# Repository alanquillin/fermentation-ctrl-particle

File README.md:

# fermentation-controller

A Particle project named fermentation-controller

## Welcome to your project!

Every new Particle project is composed of 3 important elements that you'll see have been created in your project directory for fermentation-controller.

#### ```/src``` folder:  
This is the source folder that contains the firmware files for your project. It should *not* be renamed. 
Anything that is in this folder when you compile your project will be sent to our compile service and compiled into a firmware binary for the Particle device that you have targeted.

If your application contains multiple files, they should all be included in the `src` folder. If your firmware depends on Particle libraries, those dependencies are specified in the `project.properties` file referenced below.

#### ```.ino``` file:
This file is the firmware that will run as the primary application on your Particle device. It contains a `setup()` and `loop()` function, and can be written in Wiring or C/C++. For more information about using the Particle firmware API to create firmware for your Particle device, refer to the [Firmware Reference](https://docs.particle.io/reference/firmware/) section of the Particle documentation.

#### ```project.properties``` file:  
This is the file that specifies the name and version number of the libraries that your project depends on. Dependencies are added automatically to your `project.properties` file when you add a library to a project using the `particle library add` command in the CLI or add a library in the Desktop IDE.

## Adding additional files to your project

#### Projects with multiple sources
If you would like add additional files to your application, they should be added to the `/src` folder. All files in the `/src` folder will be sent to the Particle Cloud to produce a compiled binary.

#### Projects with external libraries
If your project includes a library that has not been registered in the Particle libraries system, you should create a new folder named `/lib/<libraryname>/src` under `/<project dir>` and add the `.h`, `.cpp` & `library.properties` files for your library there. Read the [Firmware Libraries guide](https://docs.particle.io/guide/tools-and-features/libraries/) for more details on how to develop libraries. Note that all contents of the `/lib` folder and subfolders will also be sent to the Cloud for compilation.

## Compiling your project

When you're ready to compile your project, make sure you have the correct Particle device target selected and run `particle compile <platform>` in the CLI or click the Compile button in the Desktop IDE. The following files in your project folder will be sent to the compile service:

- Everything in the `/src` folder, including your `.ino` application file
- The `project.properties` file for your project
- Any libraries stored under `lib/<libraryname>/src`

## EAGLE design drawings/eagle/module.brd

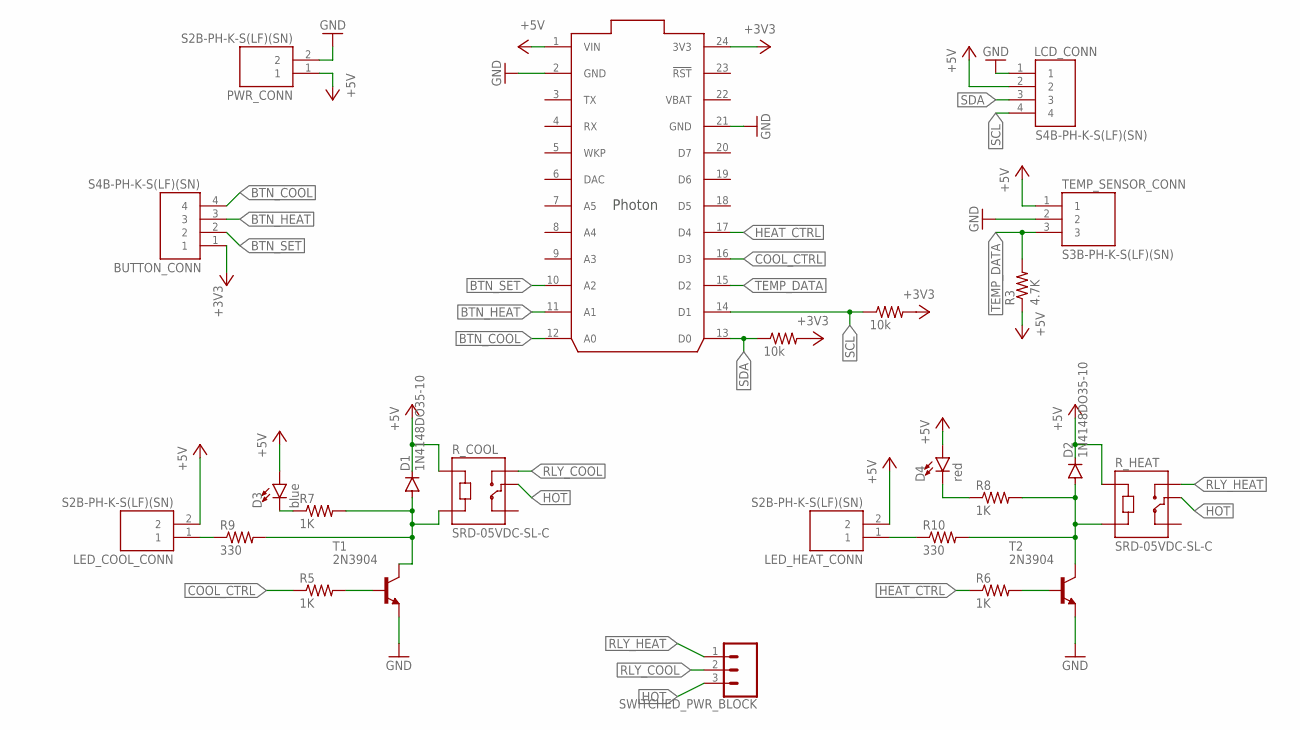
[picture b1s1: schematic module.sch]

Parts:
BUTTON_CONN: S4B-PH-K-S(LF)(SN); JST_S4B-PH-K-S(LF)(SN); MPN S4B-PH-K-S (LF)(SN)
D1, D2: 1N4148DO35-10; DO35-10; MPN 1N4148 (DO-35)
D3: blue; LED_3MM; MPN TLHB4400
D4: red; LED_3MM; MPN 4300F1LC
LCD_CONN: S4B-PH-K-S(LF)(SN); JST_S4B-PH-K-S(LF)(SN); MPN S4B-PH-K-S (LF)(SN)
LED_COOL_CONN: S2B-PH-K-S(LF)(SN); JST_S2B-PH-K-S(LF)(SN); MPN S2B-PH-K-S (LF)(SN)
LED_HEAT_CONN: S2B-PH-K-S(LF)(SN); JST_S2B-PH-K-S(LF)(SN); MPN S2B-PH-K-S (LF)(SN)
PWR_CONN: S2B-PH-K-S(LF)(SN); JST_S2B-PH-K-S(LF)(SN); MPN S2B-PH-K-S (LF)(SN)
R1, R2: 10k; 0207/10
R3: 4.7K; 0207/10
R5, R6, R7, R8: 1K; 0207/10
R9, R10: 330; 0207/10
R_COOL: SRD-05VDC-SL-C; RELAY_SRD-05VDC-SL-C
R_HEAT: SRD-05VDC-SL-C; RELAY_SRD-05VDC-SL-C
SWITCHED_PWR_BLOCK: CONN_03-SCREW-5MM; SCREWTERMINAL-5MM-3
T1, T2: 2N3904; TO92; MPN 2N3904TF
TEMP_SENSOR_CONN: S3B-PH-K-S(LF)(SN); JST_S3B-PH-K-S(LF)(SN); MPN S3B-PH-K-S (LF)(SN)
U$1: PHOTON_WITH_HEADERS; PHOTON; MPN PHOTONH

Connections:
+3V3: BUTTON_CONN.1, R1.2, R2.2, U$1.24 (3V3)
+5V: D1.C, D2.C, D3.A, D4.A, LCD_CONN.2, LED_COOL_CONN.2, LED_HEAT_CONN.2, PWR_CONN.1, R3.1, R_COOL.A1, R_HEAT.A1, TEMP_SENSOR_CONN.1, U$1.1 (VIN)
BTN_COOL: BUTTON_CONN.4, U$1.12 (A0)
BTN_HEAT: BUTTON_CONN.3, U$1.11 (A1)
BTN_SET: BUTTON_CONN.2, U$1.10 (A2)
COOL_CTRL: R5.1, U$1.16 (D3)
GND: LCD_CONN.1, PWR_CONN.2, T1.3 (E), T2.3 (E), TEMP_SENSOR_CONN.2, U$1.2 (GND), U$1.21 (GND)
HEAT_CTRL: R6.1, U$1.17 (D4)
HOT: R_COOL.COM, R_HEAT.COM, SWITCHED_PWR_BLOCK.3
unnamed: LED_COOL_CONN.1, R9.1
unnamed: LED_HEAT_CONN.1, R10.1
unnamed: D1.A, R7.2, R9.2, R_COOL.A2, T1.1 (C)
unnamed: D3.K (C), R7.1
unnamed: R5.2, T1.2 (B)
unnamed: R6.2, T2.2 (B)
unnamed: D2.A, R8.2, R10.2, R_HEAT.A2, T2.1 (C)
unnamed: D4.K (C), R8.1
RLY_COOL: R_COOL.NO, SWITCHED_PWR_BLOCK.2
RLY_HEAT: R_HEAT.NO, SWITCHED_PWR_BLOCK.1
SCL: LCD_CONN.4, R1.1, U$1.14 (D1)
SDA: LCD_CONN.3, R2.1, U$1.13 (D0)
TEMP_DATA: R3.2, TEMP_SENSOR_CONN.3, U$1.15 (D2)
VBAT: U$1.22 (VBAT)

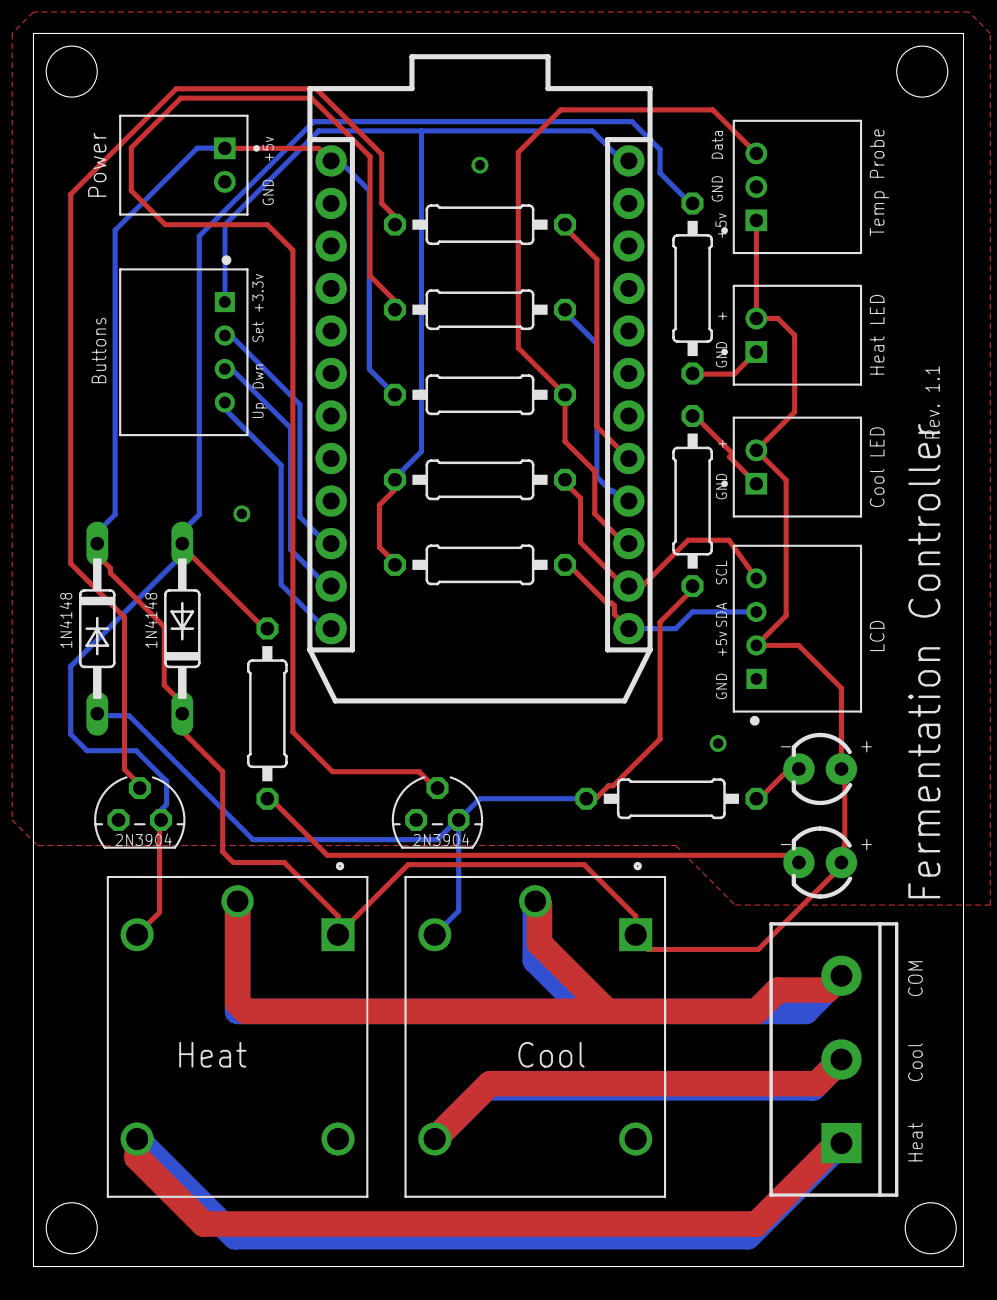
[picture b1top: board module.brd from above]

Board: 2 copper layers, 55.5 x 73.7 mm, 25 parts (0 on the bottom side), 22 nets.

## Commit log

2022-03-03 initial commit - big bang
2022-03-21 Updated to use the log library and split the heat and cool differencial
2022-03-21 Finished rev1 of the circuit board and moved to a drawings directory
2022-03-21 Added 3d model for the case
2022-03-22 add function for updating the program state via API and added missing struct keys
2022-03-22 Added new “Reset Config” menu option and functionality
2022-03-23 Added basic diagnostics screen and tests
2022-03-24 Fixed incorrect wiring for the temp probe
2022-03-25 Set SYSTEM_THREAD enabled and updated setup() to waitfor WiFi
2022-03-25 Updated loading screen and added set button on default display to allow setting target temp
2022-03-25 shortened the diagnostics button press delay

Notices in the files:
parts and their libraries:
SparkFun-LED: Licensing: Creative Commons ShareAlike 4.0 International - https://creativecommons.org/licenses/by-sa/4.0
Particle-Devices: Licensing: Designed by Particle.
